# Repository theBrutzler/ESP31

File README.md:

# ESP31
ESP32 -> ESP01

I created a board, that could fit an ESP32 on a ESP01 standard pinout. The default ESP01 programer is still working

This is the NEW 5V Version but first open the RTFM.png ;)
with V4 default is 5V operation. Works fine with 3.3 too. If u have problems make the RTFM.png

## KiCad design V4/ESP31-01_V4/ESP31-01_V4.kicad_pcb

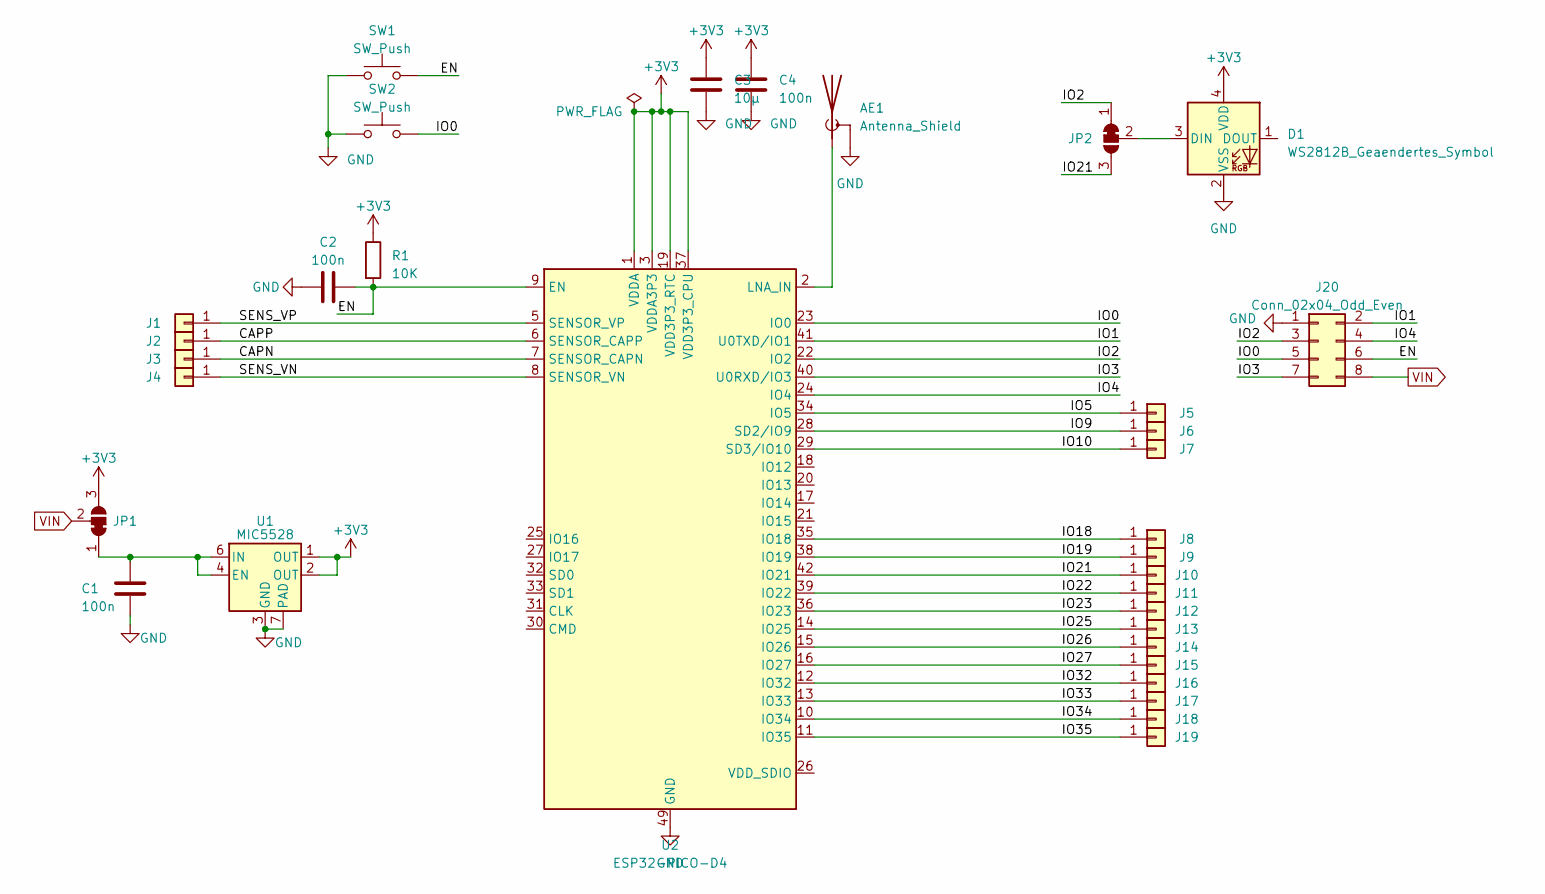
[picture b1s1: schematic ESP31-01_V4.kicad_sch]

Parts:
AE1: Antenna_Shield; Texas_SWRA117D_2.4GHz_Left
C1, C2, C4: 100n; C_0603_1608Metric; LCSC C282519
C3: 10µ; C_0603_1608Metric; LCSC C85713
D1: WS2812B_Geaendertes_Symbol; LED_Cree-PLCC4_2x2mm_CW; LCSC C965556
J1, J2, J3, J4, J5, J6, J7, J8, J9, J10, J11, J12, J13, J14, J15, J16, J17, J18, J19: Conn_01x01; CON_1x01
J20: Conn_02x04_Odd_Even; PinHeader_2x04_P2.54mm_Vertical
JP1, JP2: SolderJumper_3_Bridged12; SolderJumper-3_P1.3mm_Bridged12_RoundedPad1.0x1.5mm
R1: 10K; R_0603_1608Metric; LCSC C73809
SW1: SW_Push; microswitch; LCSC C482003
SW2: SW_Push; microswitch; LCSC C100056
U1: MIC5528; DFN-6-1EP_1.2x1.2mm_P0.4mm_EP0.3x0.94mm_PullBack; LCSC C622490
U2: ESP32-PICO-D4; QFN-48-1EP_7x7mm_P0.5mm_EP5.3x5.3mm; LCSC C193707

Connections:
+3V3: C3.2, C4.2, D1.4 (VDD), JP1.3 (B), R1.1, U1.1 (OUT), U1.2 (OUT), U2.1 (VDDA), U2.3 (VDDA3P3), U2.4 (VDDA3P3), U2.19 (VDD3P3_RTC), U2.37 (VDD3P3_CPU), U2.43 (VDDA), U2.46 (VDDA)
/CAPN: J3.1, U2.7 (SENSOR_CAPN)
/CAPP: J2.1, U2.6 (SENSOR_CAPP)
/EN: C2.1, J20.6, R1.2, SW1.2, U2.9 (EN)
/IO0: J20.5, SW2.2, U2.23 (IO0)
/IO1: J20.2, U2.41 (U0TXD/IO1)
/IO2: J20.3, JP2.1 (A), U2.22 (IO2)
/IO3: J20.7, U2.40 (U0RXD/IO3)
/IO4: J20.4, U2.24 (IO4)
/IO5: J5.1, U2.34 (IO5)
/IO9: J6.1, U2.28 (SD2/IO9)
/IO10: J7.1, U2.29 (SD3/IO10)
/IO18: J8.1, U2.35 (IO18); also elsewhere on the board
/IO19: J9.1, U2.38 (IO19)
/IO21: J10.1, JP2.3 (B), U2.42 (IO21)
/IO22: J11.1, U2.39 (IO22)
/IO23: J12.1, U2.36 (IO23)
/IO25: J13.1, U2.14 (IO25)
/IO26: J14.1, U2.15 (IO26)
/IO27: J15.1, U2.16 (IO27)
/IO32: J16.1, U2.12 (IO32)
/IO33: J17.1, U2.13 (IO33)
/IO34: J18.1, U2.10 (IO34)
/IO35: J19.1, U2.11 (IO35)
/SENS_VN: J4.1, U2.8 (SENSOR_VN)
/SENS_VP: J1.1, U2.5 (SENSOR_VP)
GND: AE1.2 (Shield), C1.1, C2.2, C3.1, C4.1, D1.2 (VSS), J20.1, SW1.1, SW2.1, U1.3 (GND), U1.7 (PAD), U2.49 (GND)
unnamed: AE1.1 (A), U2.2 (LNA_IN)
unnamed: C1.2, JP1.1 (A), U1.4 (EN), U1.6 (IN)
unnamed: D1.3 (DIN), JP2.2 (C)
VIN: J20.8, JP1.2 (C)

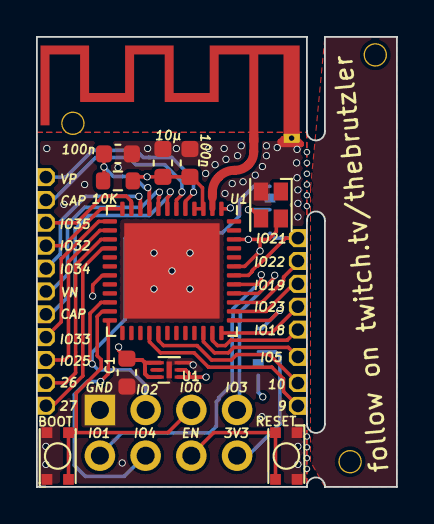
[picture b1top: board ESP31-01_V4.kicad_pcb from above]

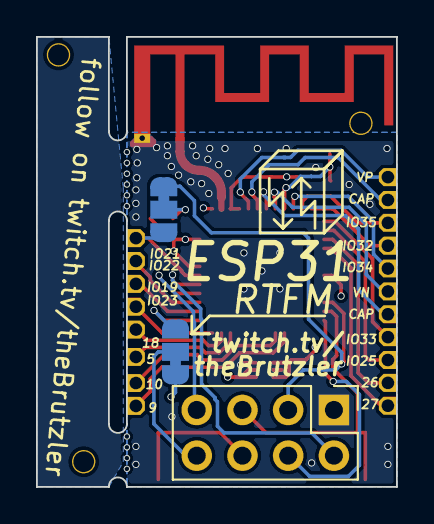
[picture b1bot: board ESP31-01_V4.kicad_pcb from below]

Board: 4 copper layers, 20.0 x 25.0 mm, 36 parts (4 on the bottom side), 31 nets.

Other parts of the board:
J8#2, J9#2: Conn_01x01; CON_1x01
SM3: SYM_Arrow45_Tiny; Symbol_kurzschlussblog

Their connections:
/IO18: J8#2.1; also elsewhere on the board

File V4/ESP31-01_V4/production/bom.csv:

Designator,Footprint,Quantity,Value,LCSC Part #
"_12, _11, _10, _9, _8, _7, _6, _5, _4, _3, _2, ",,12,,
AE1,Texas_SWRA117D_2.4GHz_Left,1,Antenna_Shield,
C1,0603,1,100n,C282519
C2,0603,1,100n,C282519
C3,0603,1,10µ,C85713
C4,0603,1,100n,C282519
D1,LED_Cree-PLCC4_2x2mm_CW,1,WS2812B_Geaendertes_Symbol,C965556
"J1, J10, J11, J12, J13, J14, J15, J16, J17, J18, J19, J2, J3, J4, J5, J6, J7, J8_2, J8, J9_2, J9",CON_1x01,21,Conn_01x01,
J20,PinHeader_2x04_P2.54mm_Vertical,1,Conn_02x04_Odd_Even,
"JP1, JP2",SolderJumper-3_P1.3mm_Bridged12_RoundedPad1.0x1.5mm,2,SolderJumper_3_Bridged12,
R1,0603,1,10K,C73809
SM3,Symbol_kurzschlussblog,1,SYM_Arrow45_Tiny,
"SW1, SW2",microswitch,2,SW_Push,C482003
U1,DFN-6-1EP_1.2x1.2mm_P0.4mm_EP0.3x0.94mm_PullBack,1,MIC5528,C622490
U2,QFN-48-1EP_7x7mm_P0.5mm_EP5.3x5.3mm,1,ESP32-PICO-D4, C193707

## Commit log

2021-08-17 initial upload
2021-10-04 Final Version
    Last ordered version. It's working :)
2021-10-05 Update pictures
2021-10-06 Create ESP31.pdf
    Upload shematic pdf
2021-10-07 corrected WS2812 Footprint
    On V1 the WS2812 was not working, because of a Footprint issue. #1
2021-10-07 Upload xlsx JLCPCB
2021-10-07 update html bom
2022-01-24 Update_V3
2022-01-24 Update README V3
2022-01-24 Update to have RTFM
2022-02-03 corrected WS2812 Footprint
    corrected WS2812 Footprint
    switched input and output of RGB LED
2022-02-03 corrected WS2812 Footprint
2023-02-14 Update to V4
    Updatet LDO to better solderable footprint
2023-02-14 update with picture
